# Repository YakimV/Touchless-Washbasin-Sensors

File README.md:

# Touchless Washbasin Sensors 🚰

The goal was to develop modern replacement sensors for **outdoor touchless washbasin systems, such as those installed at self-service car washes**. The original systems relied on obsolete electronic components that have since been discontinued, making replacement parts increasingly rare and overpriced.

*(A quick context note: all designs were engineered as drop-in upgrades for a specific, pre-existing controller architecture, where motion is signaled via **active-low logic (Logic 0 / pulled to GND = motion detected)**.)*

After testing numerous alternatives, the top options that proved best suited for high-humidity environments and real-world user interaction are:

1. **HLK-LD2416-based sensor**
2. **HLK-LD1020 + CH32V003 sensor**
3. **ToF400 / ToF200 + CH32V003 sensor**

---

### Comparison & Personal Experience

- **HLK-LD2416 (Most optimal version):**  
  I consider this the best overall choice because the sensor practically does not require an external microcontroller and can be easily configured via a standard USB-to-UART converter.  
  *(Yes, there is undeniable comedic irony in taking an advanced 24 GHz FMCW millimeter-wave radar packed with micro-motion tracking and distance-gating capabilities, only to reduce its life's purpose to the gloriously primitive task of opening a water tap when someone wants to wash their hands. It’s total overkill on paper, but in practice, it works brilliantly.)*

- **HLK-LD1020 + CH32V003:**  
  I also really like this version. In terms of raw component cost, it turns out slightly cheaper than the LD2416. However, it takes significantly longer and is much harder to assemble by hand, while objectively, there is practically no difference in real-world performance.

- **ToF400 / ToF200 + CH32V003:**  
  My least favorite. The sensor is relatively expensive and significantly compromises the enclosure's sealing and water resistance because it requires an open line of sight for the optical lens. Radar-based modules, on the other hand, detect movement directly through solid plastic, which is a massive advantage for complete waterproof sealing in plumbing fixtures.

---

### Special Mention: RCWL-0516 (Why it was an absolute failure)

While radar technology is the best direction for this application, definitely not every radar module is up to the task. Throughout the project, I went through tons of different sensors and parts, but I specifically want to single out the **RCWL-0516** because of just how exceptionally bad it turned out to be.

Even though many people online claim they work fine, in my actual experience with a batch of 20 units:
- About half were completely dead or half-broken right out of the box;
- Another portion had a detection range of barely half a meter;
- Only a tiny fraction behaved relatively predictably.

Between the massive defect rate, bulky footprint, and outdated design, out of everything I tested, this one stands out as completely unusable for any reliable hardware build.

### LD2416-based sensor:

https://github.com/user-attachments/assets/3fb2ff55-c5b9-49b8-b7ec-d0e878508fb5

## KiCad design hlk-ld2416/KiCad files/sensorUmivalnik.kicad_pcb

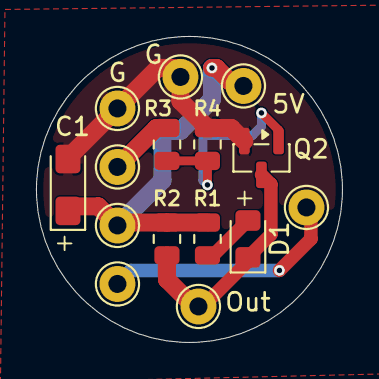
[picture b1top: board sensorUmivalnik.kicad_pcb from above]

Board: 2 copper layers, 17.0 x 17.0 mm, 15 parts (0 on the bottom side), 7 nets.

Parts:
5V, 5V#2: Conn_01x01_Pin; TestPoint_THTPad_D2.0mm_Drill1.0mm
C1: 47uf; CP_EIA-3216-18_Kemet-A_HandSolder
D1: LED; LED_0805_2012Metric_Pad1.15x1.40mm_HandSolder
G: Conn_01x01_Pin; TestPoint_THTPad_D2.0mm_Drill1.0mm
G#2: Conn_01x01_Pin; TestPoint_THTPad_D2.0mm_Drill1.0mm
Out: Conn_01x01_Pin; TestPoint_THTPad_D2.0mm_Drill1.0mm
Outraw: Conn_01x01_Pin; TestPoint_THTPad_D2.0mm_Drill1.0mm
PROG: Conn_01x01_Pin; TestPoint_THTPad_D2.0mm_Drill1.0mm
PROG#2: Conn_01x01_Pin; TestPoint_THTPad_D2.0mm_Drill1.0mm
Q2: IRLML0030; SOT-23
R1, R2, R3: 1k; R_0805_2012Metric
R4: 10k; R_0805_2012Metric

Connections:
+5V: 5V.1 (Pin_1_1), 5V#2.1 (Pin_1_1), C1.1, R1.1, R2.1
/OUT: D1.1 (K), Out.1 (Pin_1_1), Q2.3 (D), R2.2
/PROG: PROG.1 (Pin_1_1), PROG#2.1 (Pin_1_1)
GND: C1.2, G.1 (Pin_1_1), G#2.1 (Pin_1_1), Q2.2 (S), R4.2
unnamed: D1.2 (A), R1.2
unnamed: Outraw.1 (Pin_1_1), R3.1
unnamed: Q2.1 (G), R3.2, R4.1
